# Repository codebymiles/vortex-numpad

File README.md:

# vortex-numpad
 Custom Vortex 22-key switch tester numpad PCB

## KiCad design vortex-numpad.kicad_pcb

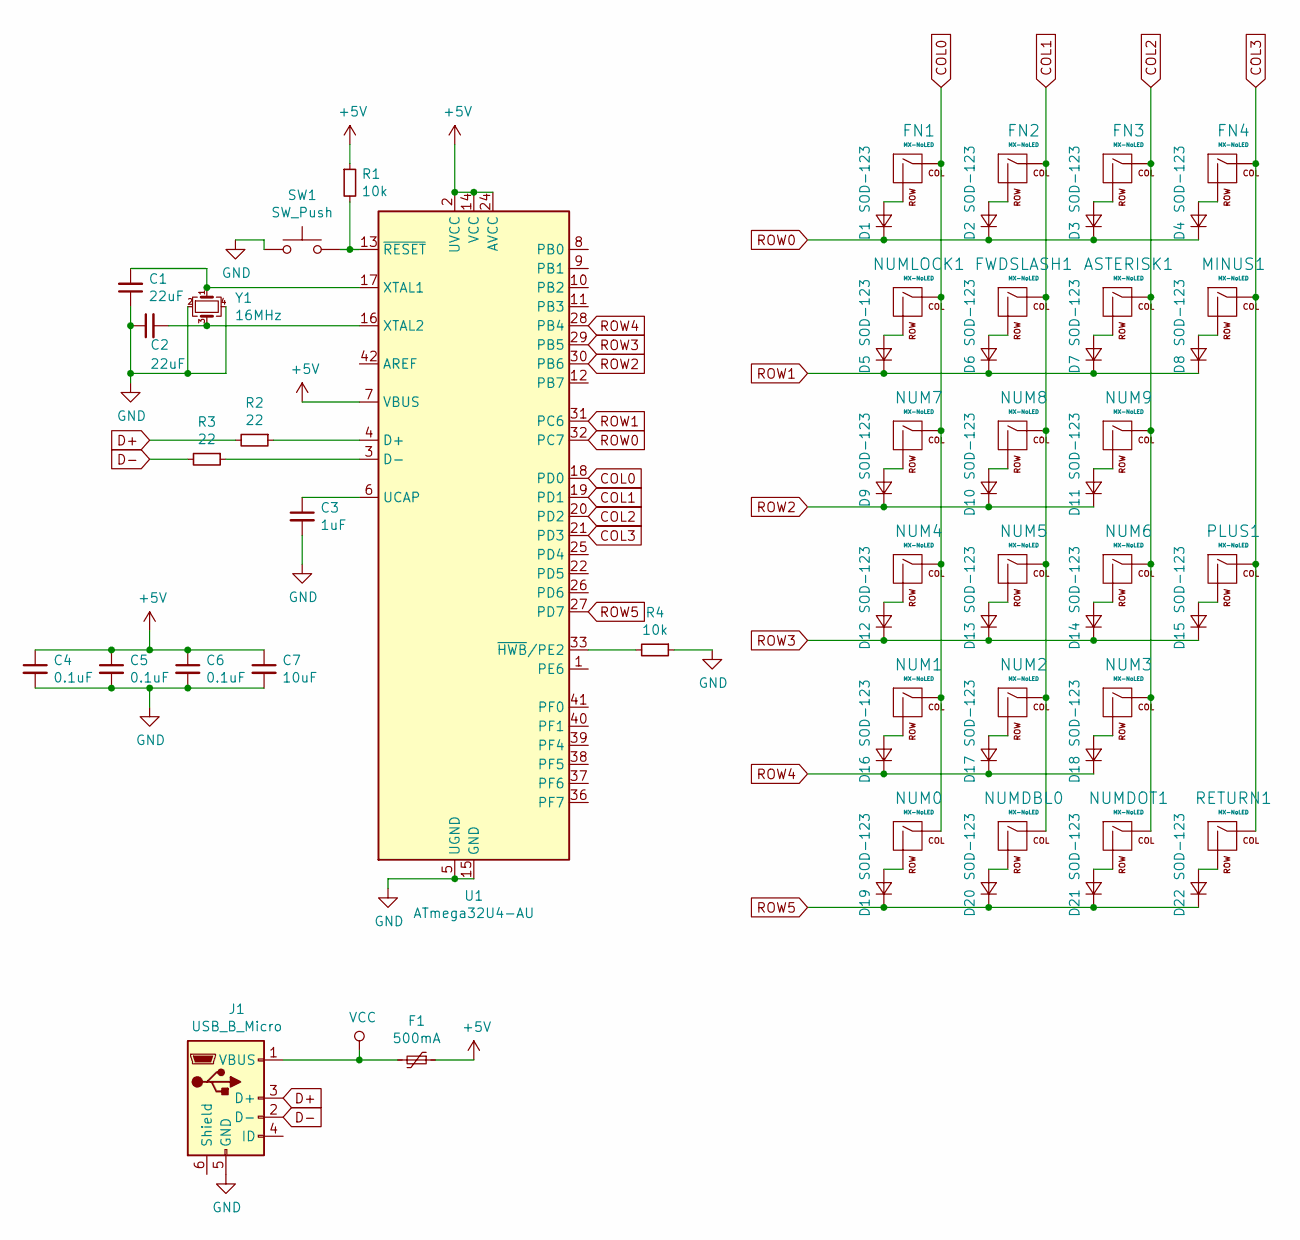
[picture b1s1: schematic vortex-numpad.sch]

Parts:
ASTERISK1: MX-NoLED; MX-1U-NoLED
C1, C2: 22uF; D_SOD-123
C3: 1uF; D_SOD-123
C4, C5, C6: 0.1uF; D_SOD-123
C7: 10uF; D_SOD-123
D1, D2, D3, D4, D5, D6, D7, D8, D9, D10, D11, D12, D13, D14, D15, D16, D17, D18, D19, D20, D21, D22: SOD-123; D_SOD-123
F1: 500mA; Fuse_1206_3216Metric
FN1, FN2, FN3, FN4: MX-NoLED; MX-1U-NoLED
FWDSLASH1: MX-NoLED; MX-1U-NoLED
J1: USB_B_Micro; USB_Micro-B_Molex-105017-0001
MINUS1: MX-NoLED; MX-1U-NoLED
NUM0, NUM1, NUM2, NUM3, NUM4, NUM5, NUM6, NUM7, NUM8, NUM9: MX-NoLED; MX-1U-NoLED
NUMDBL0: MX-NoLED; MX-1U-NoLED
NUMDOT1: MX-NoLED; MX-1U-NoLED
NUMLOCK1: MX-NoLED; MX-1U-NoLED
PLUS1: MX-NoLED; MX-2U-ReversedStabilizers-NoLED
R1, R4: 10k; R_0805_2012Metric
R2, R3: 22; R_0805_2012Metric
RETURN1: MX-NoLED; MX-2U-ReversedStabilizers-NoLED
SW1: SW_Push; SKQG-1155865
U1: ATmega32U4-AU; TQFP-44_10x10mm_P0.8mm
Y1: 16MHz; Crystal_SMD_3225-4Pin_3.2x2.5mm

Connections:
+5V: C4.1, C5.1, C6.1, C7.1, F1.1, R1.1, U1.2 (UVCC), U1.7 (VBUS), U1.14 (VCC), U1.24 (AVCC), U1.34 (VCC), U1.44 (AVCC)
COL0: FN1.1 (COL), NUM0.1 (COL), NUM1.1 (COL), NUM4.1 (COL), NUM7.1 (COL), NUMLOCK1.1 (COL), U1.18 (PD0)
COL1: FN2.1 (COL), FWDSLASH1.1 (COL), NUM2.1 (COL), NUM5.1 (COL), NUM8.1 (COL), NUMDBL0.1 (COL), U1.19 (PD1)
COL2: ASTERISK1.1 (COL), FN3.1 (COL), NUM3.1 (COL), NUM6.1 (COL), NUM9.1 (COL), NUMDOT1.1 (COL), U1.20 (PD2)
COL3: FN4.1 (COL), MINUS1.1 (COL), PLUS1.1 (COL), RETURN1.1 (COL), U1.21 (PD3)
D+: J1.3 (D+), R2.2
D-: J1.2 (D-), R3.2
GND: C1.1, C2.1, C3.2, C4.2, C5.2, C6.2, C7.2, J1.5 (GND), R4.1, SW1.1, U1.5 (UGND), U1.15 (GND), U1.23 (GND), U1.35 (GND), U1.43 (GND), Y1.2, Y1.4
unnamed: ASTERISK1.2 (ROW), D7.2 (A)
unnamed: C1.2, U1.17 (XTAL1), Y1.1
unnamed: C2.2, U1.16 (XTAL2), Y1.3
unnamed: C3.1, U1.6 (UCAP)
unnamed: D1.2 (A), FN1.2 (ROW)
unnamed: D2.2 (A), FN2.2 (ROW)
unnamed: D3.2 (A), FN3.2 (ROW)
unnamed: D4.2 (A), FN4.2 (ROW)
unnamed: D5.2 (A), NUMLOCK1.2 (ROW)
unnamed: D6.2 (A), FWDSLASH1.2 (ROW)
unnamed: D8.2 (A), MINUS1.2 (ROW)
unnamed: D9.2 (A), NUM7.2 (ROW)
unnamed: D10.2 (A), NUM8.2 (ROW)
unnamed: D11.2 (A), NUM9.2 (ROW)
unnamed: D12.2 (A), NUM4.2 (ROW)
unnamed: D13.2 (A), NUM5.2 (ROW)
unnamed: D14.2 (A), NUM6.2 (ROW)
unnamed: D15.2 (A), PLUS1.2 (ROW)
unnamed: D16.2 (A), NUM1.2 (ROW)
unnamed: D17.2 (A), NUM2.2 (ROW)
unnamed: D18.2 (A), NUM3.2 (ROW)
unnamed: D19.2 (A), NUM0.2 (ROW)
unnamed: D20.2 (A), NUMDBL0.2 (ROW)
unnamed: D21.2 (A), NUMDOT1.2 (ROW)
unnamed: D22.2 (A), RETURN1.2 (ROW)
unnamed: R1.2, SW1.2, U1.13 (~RESET)
unnamed: R2.1, U1.4 (D+)
unnamed: R3.1, U1.3 (D-)
unnamed: R4.2, U1.33 (~HWB~/PE2)
ROW0: D1.1 (K), D2.1 (K), D3.1 (K), D4.1 (K), U1.32 (PC7)
ROW1: D5.1 (K), D6.1 (K), D7.1 (K), D8.1 (K), U1.31 (PC6)
ROW2: D9.1 (K), D10.1 (K), D11.1 (K), U1.30 (PB6)
ROW3: D12.1 (K), D13.1 (K), D14.1 (K), D15.1 (K), U1.29 (PB5)
ROW4: D16.1 (K), D17.1 (K), D18.1 (K), U1.28 (PB4)
ROW5: D19.1 (K), D20.1 (K), D21.1 (K), D22.1 (K), U1.27 (PD7)
VCC: F1.2, J1.1 (VBUS)

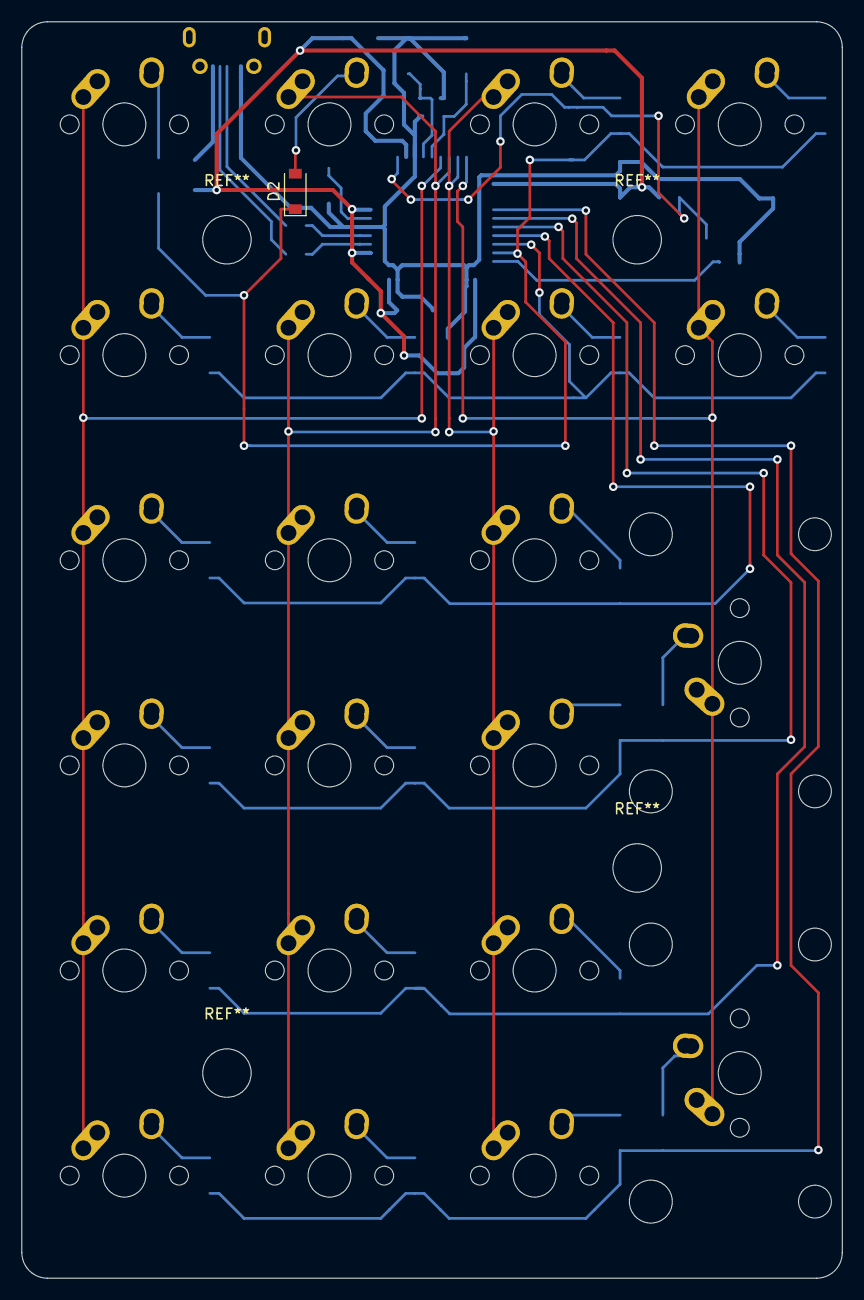
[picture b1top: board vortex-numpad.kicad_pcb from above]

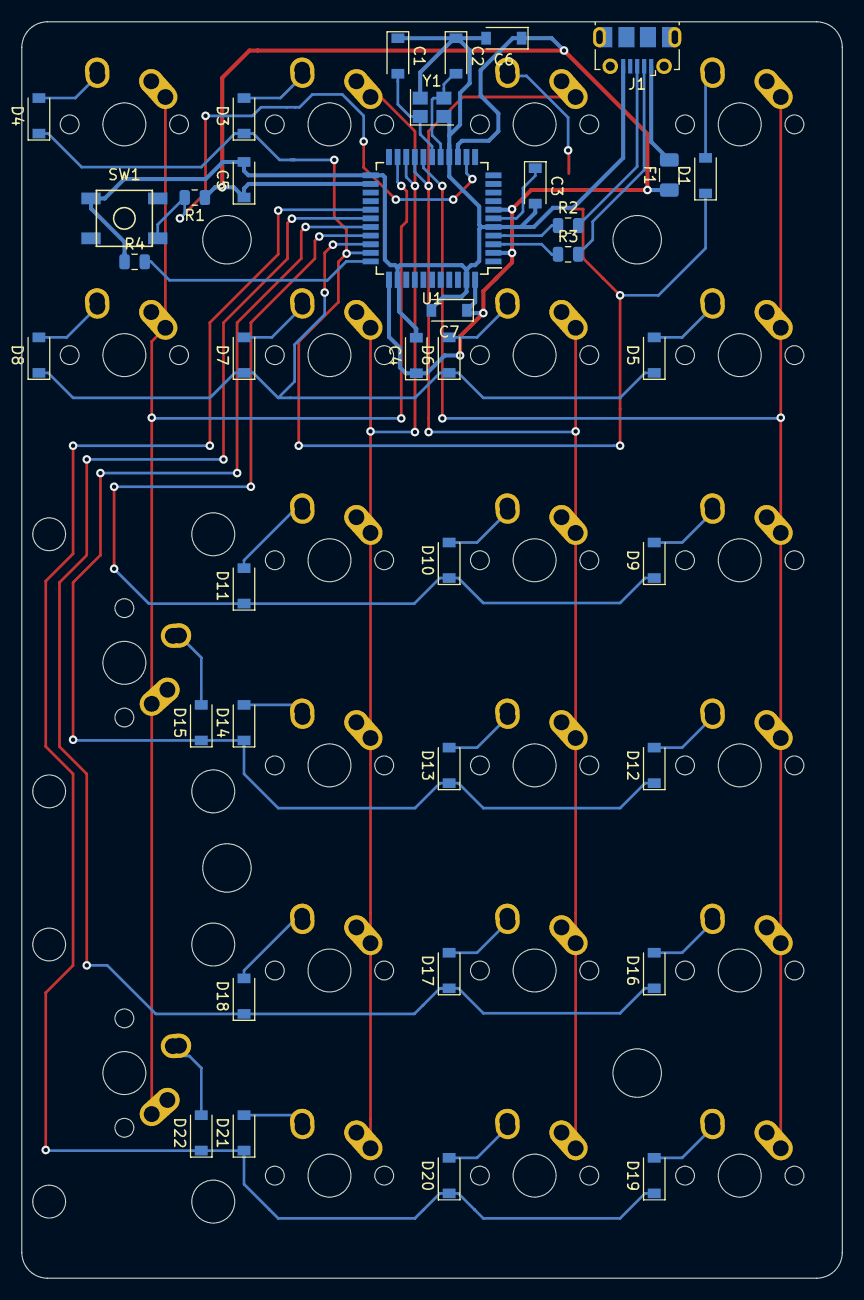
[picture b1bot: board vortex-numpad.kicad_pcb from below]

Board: 2 copper layers, 76.2 x 116.7 mm, 60 parts (37 on the bottom side), 44 nets.

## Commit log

2019-08-27 Add ai03 submodules
2019-08-27 Initialise kicad project
2019-08-27 Add footprint libraries
2019-08-28 Initial Schematic
2019-08-29 Schematic laid out
2019-08-29 Pins assigned, keys named
2019-08-31 Assign footprints
2019-08-31 PCB Editor Preferences
2019-08-31 Initial PCB layout
2019-08-31 Most switch tracks in place, terrible
2019-09-04 Initial traces all done
2019-09-04 Fixed mounting holes and associated spacing
2019-09-04 All layers on for reddit
